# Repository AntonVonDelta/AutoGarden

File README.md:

# AutoGarden
Codul si schema unui circuit pentru automatizarea gradinii. 
Circuitul este potrivit daca:
 - Ai o pompa de apa ce alimenteaza un bazin separat (pompa pornita fie dintr-un contactor fie cu ajutorul unui presostat cu o electrovalva de 220V)
 - Doresti din timp in timp sa uzi gradina pe zone folosind electrovalve de 12V
 - Doresti o interfata web pentru a controla tot sistemul si pentru a programa pe ore si zile udarea gradinii
 - Doresti un proiect autonom in lipsa internetului

Desigur pot fi construite doar sectiuni din proiect care sa excluda, de exemplu, contactorul.

# Componente electrice
 - O sursa de alimentare ce poate furniza 12V cu 3A, 5V cu 1A
 - ESP32 NodeMCU
 - Breadboard
 - 8 diode
 - 5 mosfeturi IRLZ44N.  ( **Atentie!** Acesta e un mosfet de nivel TTL adica de 5V. Nu-l incurcati cu IRFZ44N )
 - 8 rezistente de 10k
 - 5 rezistente de 100ohm
 - 3 tranzistori BC547 sau echivalent cu `hFE ~ 100`
 - 3 relee 12V 0.36W/400ohm ( **obligatoriu putere mai mica sau egala decat aceasta** )
 - Ceas RTC modul DS3231 ( **obligatoriu** )
 - 1 contactor
 - 5 electrovalve 12V 5W/28ohm

# Alimentare
Alimentarea de joasa tensiune se face printr-un conector de 3 pini: 12V, 5V si GND(minus).
Alimentarea de 220V se face la locurile marcate in schema ca `SURSA_AC_NUL` si `SURSA_AC_FAZA`

# Caracteristici
 - Controlul de la distanta a intregului sistem
 - 50 de posibile programari ale electrovalvelor cu variabilele: zile de activitate, intervalul de functionare si electrovalva/releul ce va fi activat.
 - 5 porturi pentru electrovalve la 12V
 - 3 porturi la 220V cu proprietatile (activate de relee):
   - 1 port pentru deschiderea unei electrovalve la 220V ( la care este conectata pompa de apa )
   - 1 port conectat la un contactor ce permite deschiderea directa a pompei sau a altor aparate de putere
   - 1 port pentru orice alta necesitate
 - Posibilitatea in cod si in schema electronica de a mai adauga porturi de 12V sau relee.
 - Timp sincronizat de pe internet. In cazul lipsei de conectiune la internet ceasul intern este folosit
 - Reprogramare sigura de la distanta cu parola ( Nu este nevoie sa reprogramati microprocesorul prin usb )
 - O serie de comenzi pentru "depanarea" de la distanta. Optiunile includ:
   - puterea semnalului
   - dimensiunea curenta a heap-ului
   - evenimentul ce a determinat deschiderea microprocesorului (POWER_ON, RESET, WATCHDOG, etc)
   - etc.  
 - Auto-resetarea in cazul in care se blocheaza microprocesorul
 - Salvarea tuturor setarilor in memorie non-volatila
 - Auto-reconectarea la reteaua WIFI
 - Colorarea in albastru pe imaginea gradinii a zonei active

# Instalare software
Sunt necesari cativa pasi pentru a putea folosi codul:
 - in `ESP32_AutoGradina/ESP32_AutoGradina.ino` schimba valorile:
   - `YOUR SSID` cu SSID-ul tau
   - `YOUR PASSWORD` cu parola WIFI-ului
   - `YOUR ARDUINO OTA PASSWORD` cu un cod lung si unic. Aceasta va fi parola ceruta de Arduino pentru a reprograma microprocesorul de la distanta.  
 - schimbarea imaginii gradinii. Vezi sectiunea `Instructiuni`
 - copierea librariilor din folderul `libraries` in folderul `libraries` din Arduino

# Pagini web
Exista 3 ferestre:
 - Fereastra `Timer` cu fisierele corespunzatoare: 
   - `index.html`
   - `script.js`
   - `style.css`
 - Fereastra `Gradina` cu fisierele:
   - `gradina.html`
   - `script_garden.js`
   - `style.css`
 - Fereastra de debug:
   - `debug_page.html`
   - `debug_script.js`
 
De asemenea exista un fisier `garden.svg` ce contine o imagine ( pe post de exemplu ) a pozitiilor tuturor electrovalvelor. Va trebui sa-l modifici.

## Instructiuni
Pentru a modifica fiserele html/stiluri sau javascript:
 - Modificati fisierul corespunzator din folderul `www`
 - Copiati continutul noului fisier in fereastra uneltei `Compress HTML Tool`. Unealta va detecta automat tipul limbajului si il va comprima pentru a fi folosit in Arduino
 - Copiati versiunea comprimata in fisierul `ESP32_AutoGradina/FileData.h` in variabila corespunzatoare.

Pentru a modifica imaginea gradinii:
 - Creati o imagine svg a gradinii
 - Deschideti imaginea intr-un text editor si copiati continutul in fisierul `www/gradina.html` in locul tagului `<svg>`. ( **Atentie!** Pastrati optiunile din acest tag precum `viewBox` si `width` )
 - Modificati in fisierul `www/script_garden.js` lista numita `garden_zones` cu id-urile dreptunghiurilor corespunzatoare zonelor udate. ( Le puteti gasi in fisiserul `svg` pe linii de tipul `<rect id="svg_1" height="323.99998" width="61.00001" y="-2.05" x="1.5" stroke-width="1.5" stroke="#000" fill="#667856"/>`. Copiati doar valoarea lui `id` )

# Schematica

# Interfata web
### Timer

<hr>

### Gradina

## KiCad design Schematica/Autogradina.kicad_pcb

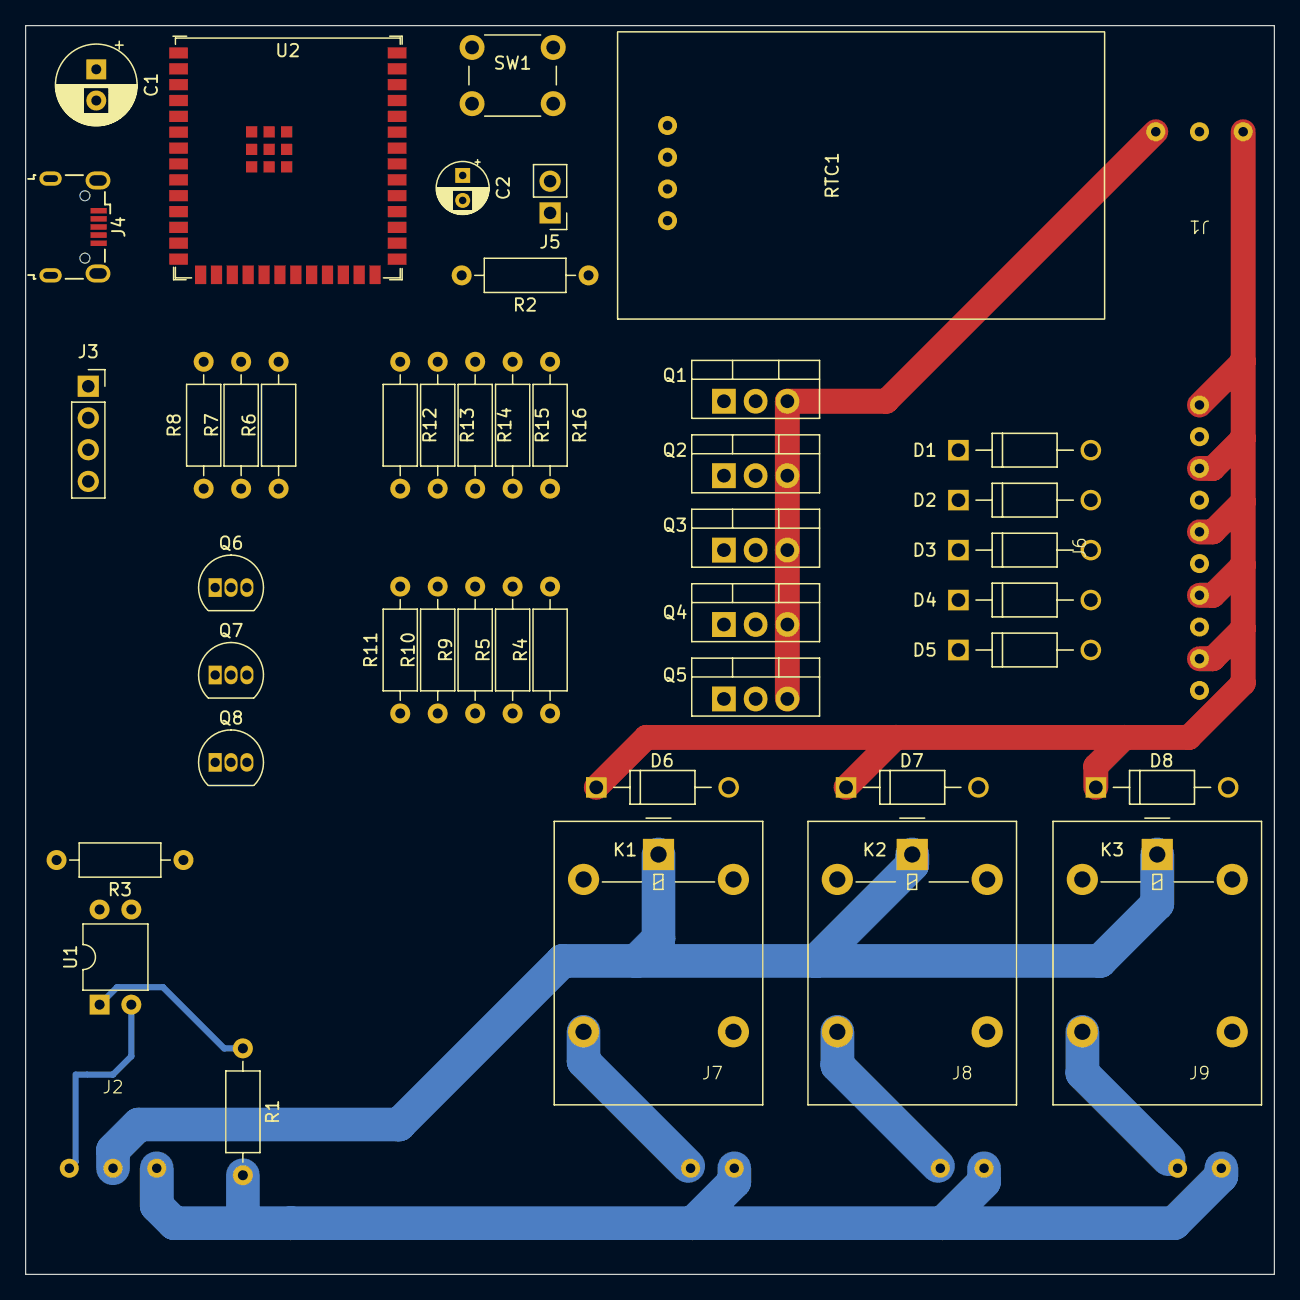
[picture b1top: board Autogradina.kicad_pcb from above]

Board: 2 copper layers, 100.0 x 100.0 mm, 51 parts (1 on the bottom side), 44 nets.

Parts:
C1: 22uF; CP_Radial_D6.3mm_P2.50mm
C2: 1uF; CP_Radial_D4.0mm_P2.00mm
D1, D2, D3, D4, D5, D6, D7, D8: D; 1N4007
J1: Power_Connector; Connector_RND_205-00113_3Pins_3.5mm
J2: AC_Connector; Connector_RND_205-00113_3Pins_3.5mm
J3: UART_Connector; PinSocket_1x04_P2.54mm_Vertical
J4: USB_B_Micro; USB_Micro-B_Wuerth_629105150521
J5: Boot_Jumper; PinHeader_1x02_P2.54mm_Vertical
J6: Ports_Connector; Connector_Wire-To-Board_10Pins_2.54mm
J7, J8, J9: Conn_01x02_Socket; Connector_RND_205-00113_2Pins_3.5mm
K1, K2, K3: G5LE-1; Relay_SPDT_Omron-G5LE-1
NT1: NetTie_2; NetTie-2_SMD_Pad0.5mm
Q1, Q2, Q3, Q4, Q5: IRLZ44N; TO-220-3_Vertical
Q6, Q7, Q8: BC547; TO-92_Inline
R1: 180k; R_Axial_DIN0207_L6.3mm_D2.5mm_P10.16mm_Horizontal
R2, R3, R4, R5, R9, R10, R11: 10k; R_Axial_DIN0207_L6.3mm_D2.5mm_P10.16mm_Horizontal
R6, R7, R8: 5k; R_Axial_DIN0207_L6.3mm_D2.5mm_P10.16mm_Horizontal
R12, R13, R14, R15, R16: 100; R_Axial_DIN0207_L6.3mm_D2.5mm_P10.16mm_Horizontal
RTC1: DS3231; RTC-Module
SW1: Reset_Btn; SW_PUSH_6mm
U1: PC817; DIP-4_W7.62mm
U2: ESP32-S3-WROOM-1; ESP32-S3-WROOM-1U

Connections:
3.3V: C1.1, J1.2, J3.4, R2.1, R3.1, RTC1.3 (VCC), U2.2 (3V3)
12V: D1.1 (K), D2.1 (K), D3.1 (K), D4.1 (K), D5.1 (K), D6.1 (K), D7.1 (K), D8.1 (K), J1.1, J6.2, J6.4, J6.6, J6.8, J6.10, K1.2, K2.2, K3.2
AC_G: J2.1, NT1.1
AC_L: J2.2, K1.1, K2.1, K3.1
AC_N: J2.3, J7.2, J8.2, J9.2, R1.2
GND: C1.2, C2.1, J1.3, J3.1, J4.5 (GND), J4.6 (Shield), J5.1, Q1.3 (S), Q2.3 (S), Q3.3 (S), Q4.3 (S), Q5.3 (S), Q6.3 (E), Q7.3 (E), Q8.3 (E), R4.1, R5.1, R9.1, R10.1, R11.1, RTC1.4 (GND), SW1.1, U1.3, U2.1 (GND), U2.15 (GPIO3/TOUCH3/ADC1_CH2), U2.40 (GND), U2.41 (GND)
Mosfet_Port1: R12.1, U2.20 (GPIO12/TOUCH12/ADC2_CH1/FSPICLK/FSPIIO6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)
Mosfet_Port2: R13.1, U2.21 (GPIO13/TOUCH13/ADC2_CH2/FSPIQ/FSPIIO7/S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)
Mosfet_Port3: R14.1, U2.22 (GPIO14/TOUCH14/ADC2_CH3/FSPIWP/FSPIDQS/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)
Mosfet_Port4: R15.1, U2.10 (GPIO17/U1TXD/ADC2_CH6)
Mosfet_Port5: R16.1, U2.11 (GPIO18/U1RXD/ADC2_CH7/CLK_OUT3)
N_To_Ground_Probe: R3.2, U1.4, U2.39 (GPIO1/TOUCH1/ADC1_CH0)
unnamed: D1.2 (A), J6.9, Q1.2 (D)
unnamed: D2.2 (A), J6.7, Q2.2 (D)
unnamed: D3.2 (A), J6.5, Q3.2 (D)
unnamed: D4.2 (A), J6.3, Q4.2 (D)
unnamed: D5.2 (A), J6.1, Q5.2 (D)
unnamed: D6.2 (A), K1.5, Q6.1 (C)
unnamed: D7.2 (A), K2.5, Q7.1 (C)
unnamed: D8.2 (A), K3.5, Q8.1 (C)
unnamed: J3.2, U2.37 (U0TXD/GPIO43/CLK_OUT1)
unnamed: J3.3, U2.36 (U0RXD/GPIO44/CLK_OUT2)
unnamed: J4.3 (D+), U2.14 (GPIO20/U1CTS/ADC2_CH9/CLK_OUT1/USB_D+)
unnamed: J4.2 (D-), U2.13 (GPIO19/U1RTS/ADC2_CH8/CLK_OUT2/USB_D-)
unnamed: J5.2, U2.27 (GPIO0/BOOT)
unnamed: J7.1, K1.3
unnamed: J8.1, K2.3
unnamed: J9.1, K3.3
unnamed: NT1.2, U1.2
unnamed: Q1.1 (G), R11.2, R12.2
unnamed: Q2.1 (G), R10.2, R13.2
unnamed: Q3.1 (G), R9.2, R14.2
unnamed: Q4.1 (G), R5.2, R15.2
unnamed: Q5.1 (G), R4.2, R16.2
unnamed: Q6.2 (B), R8.1
unnamed: Q7.2 (B), R7.1
unnamed: Q8.2 (B), R6.1
unnamed: R1.1, U1.1
unnamed: C2.2, R2.2, SW1.2, U2.3 (EN)
RELAY1_CONTROL: R8.2, U2.12 (GPIO8/TOUCH8/ADC1_CH7/SUBSPICS1)
RELAY2_CONTROL: R7.2, U2.17 (GPIO9/TOUCH9/ADC1_CH8/FSPIHD/SUBSPIHD)
RELAY3_CONTROL: R6.2, U2.18 (GPIO10/TOUCH10/ADC1_CH9/FSPICS0/FSPIIO4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)
RTC_CLOCK: RTC1.1 (SCL), U2.28 (SPIIO6/GPIO35/FSPID/SUBSPID)
RTC_DATA: RTC1.2 (SDA), U2.29 (SPIIO7/GPIO36/FSPICLK/SUBSPICLK)

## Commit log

2021-09-08 First
2021-09-09 Updated code
2021-09-10 Fixed missing requirements
2022-01-23 Updated kicad files
2023-04-15 Schematic updates; Created board
2023-04-15 Schematic update and image
2023-04-16 Updated schematic, board; Almost finished board
2023-04-28 Routing changes
2023-04-28 Repaired too small tracks
2023-04-29 Improvements
2023-04-29 Added gnd fill areas
2023-04-30 Finished up
2023-04-30 Removed most of traces; Updated schematci
